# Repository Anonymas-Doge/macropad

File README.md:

# Macropad

9 key macropad with rotary encoder, OLED DISPLAY, and WS2812B LEDs. Uses QMK firmware.

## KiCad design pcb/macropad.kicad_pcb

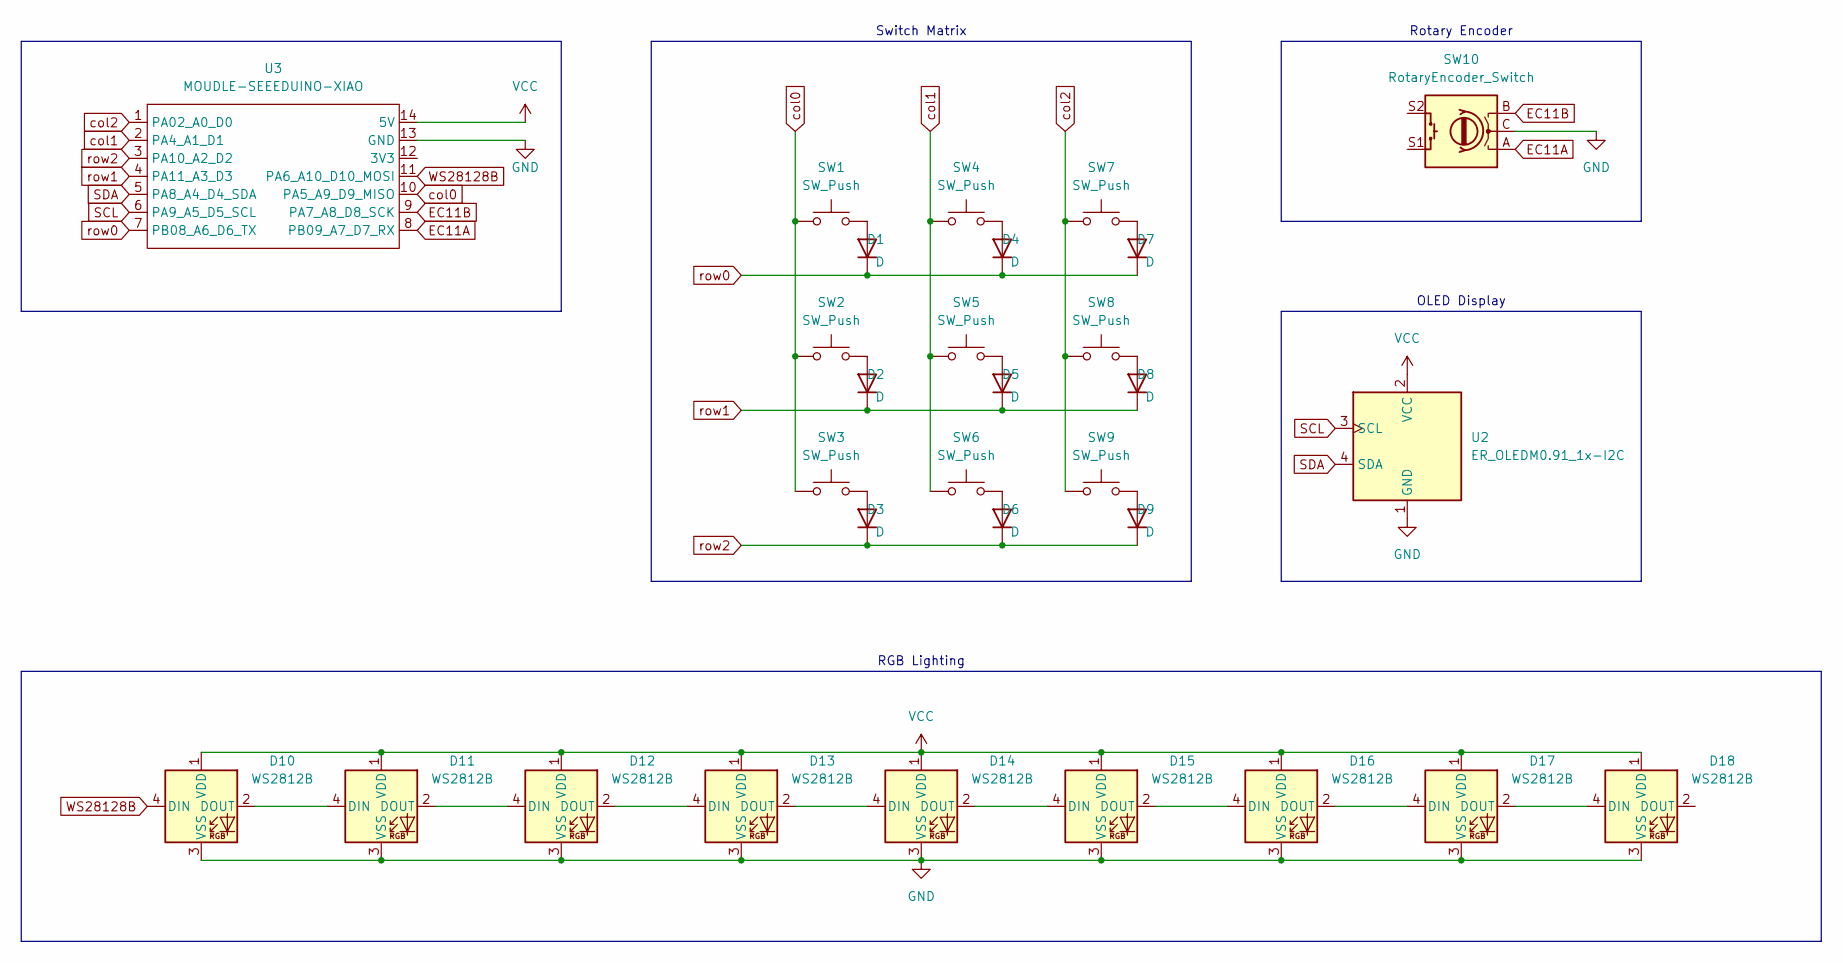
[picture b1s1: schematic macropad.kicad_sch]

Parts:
D1, D2, D3, D4, D5, D6, D7, D8, D9: D; D_DO-35_SOD27_P7.62mm_Horizontal
D10, D11, D12, D13, D14, D15, D16, D17, D18: WS2812B; SK6812MINI-E_fixed
SW1, SW2, SW3, SW4, SW5, SW6, SW7, SW8, SW9: SW_Push; SW_Cherry_MX_1.00u_PCB
SW10: RotaryEncoder_Switch; RotaryEncoder_Alps_EC11E-Switch_Vertical_H20mm
U2: ER_OLEDM0.91_1x-I2C; SSD1306-0.91-OLED-4pin-128x32
U3: MOUDLE-SEEEDUINO-XIAO; XIAO-Generic-Hybrid-14P-2.54-21X17.8MM

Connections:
EC11A: SW10.A, U3.8 (PB09_A7_D7_RX)
EC11B: SW10.B, U3.9 (PA7_A8_D8_SCK)
GND: D10.3 (VSS), D11.3 (VSS), D12.3 (VSS), D13.3 (VSS), D14.3 (VSS), D15.3 (VSS), D16.3 (VSS), D17.3 (VSS), D18.3 (VSS), SW10.C, U2.1 (GND), U3.13 (GND)
unnamed: D1.2 (A), SW1.2
unnamed: D2.2 (A), SW2.2
unnamed: D3.2 (A), SW3.2
unnamed: D4.2 (A), SW4.2
unnamed: D5.2 (A), SW5.2
unnamed: D6.2 (A), SW6.2
unnamed: D7.2 (A), SW7.2
unnamed: D8.2 (A), SW8.2
unnamed: D9.2 (A), SW9.2
unnamed: D10.2 (DOUT), D11.4 (DIN)
unnamed: D11.2 (DOUT), D12.4 (DIN)
unnamed: D12.2 (DOUT), D13.4 (DIN)
unnamed: D13.2 (DOUT), D14.4 (DIN)
unnamed: D14.2 (DOUT), D15.4 (DIN)
unnamed: D15.2 (DOUT), D16.4 (DIN)
unnamed: D16.2 (DOUT), D17.4 (DIN)
unnamed: D17.2 (DOUT), D18.4 (DIN)
SCL: U2.3 (SCL), U3.6 (PA9_A5_D5_SCL)
SDA: U2.4 (SDA), U3.5 (PA8_A4_D4_SDA)
VCC: D10.1 (VDD), D11.1 (VDD), D12.1 (VDD), D13.1 (VDD), D14.1 (VDD), D15.1 (VDD), D16.1 (VDD), D17.1 (VDD), D18.1 (VDD), U2.2 (VCC), U3.14 (5V)
WS28128B: D10.4 (DIN), U3.11 (PA6_A10_D10_MOSI)
col0: SW1.1, SW2.1, SW3.1, U3.10 (PA5_A9_D9_MISO)
col1: SW4.1, SW5.1, SW6.1, U3.2 (PA4_A1_D1)
col2: SW7.1, SW8.1, SW9.1, U3.1 (PA02_A0_D0)
row0: D1.1 (K), D4.1 (K), D7.1 (K), U3.7 (PB08_A6_D6_TX)
row1: D2.1 (K), D5.1 (K), D8.1 (K), U3.4 (PA11_A3_D3)
row2: D3.1 (K), D6.1 (K), D9.1 (K), U3.3 (PA10_A2_D2)

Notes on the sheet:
OLED Display
Switch Matrix
RGB Lighting
Rotary Encoder

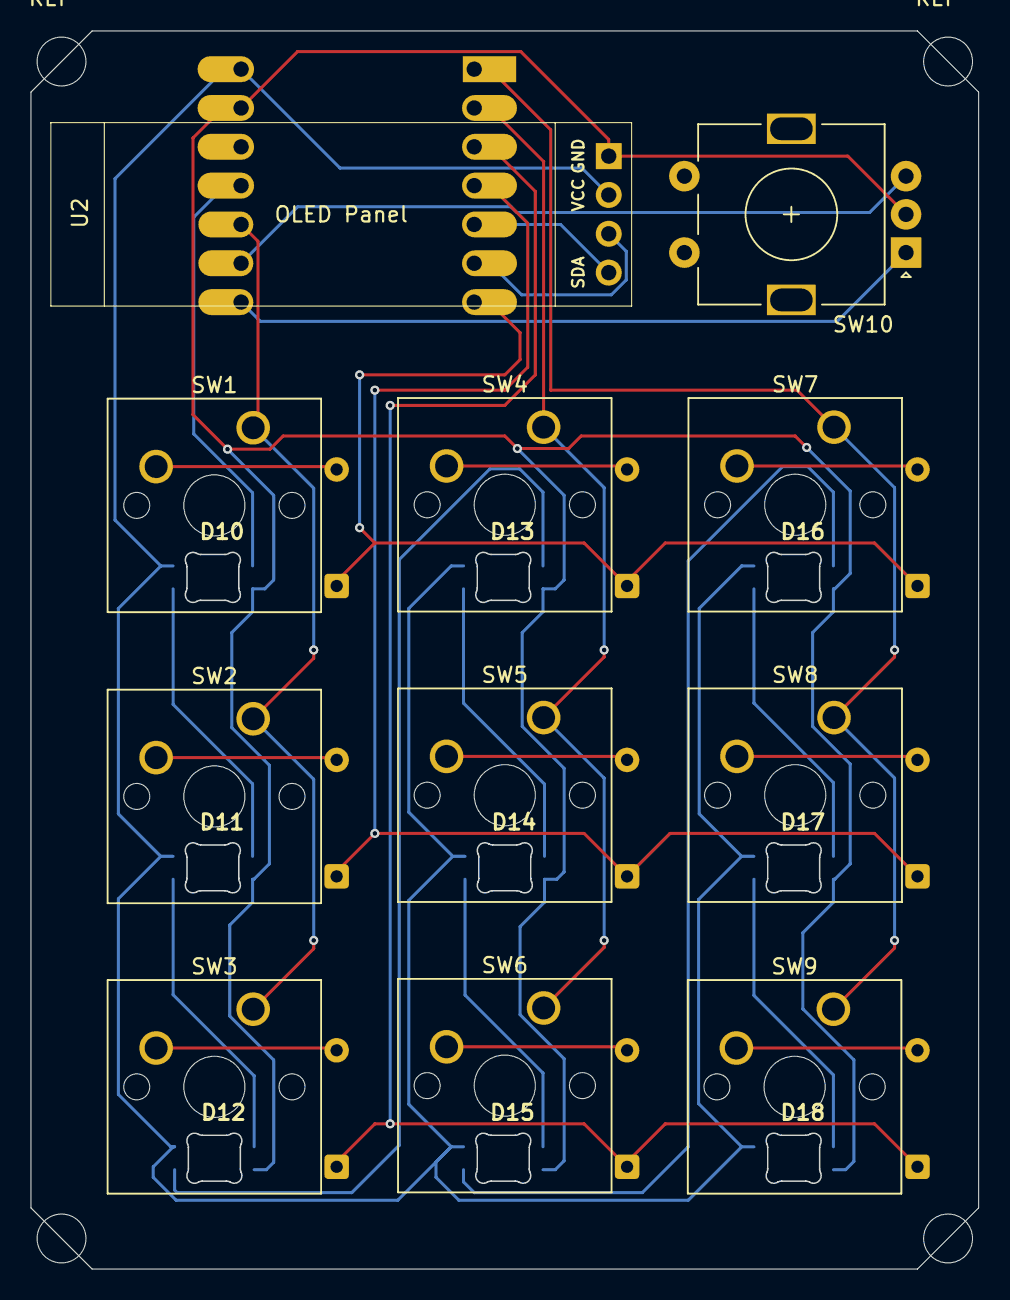
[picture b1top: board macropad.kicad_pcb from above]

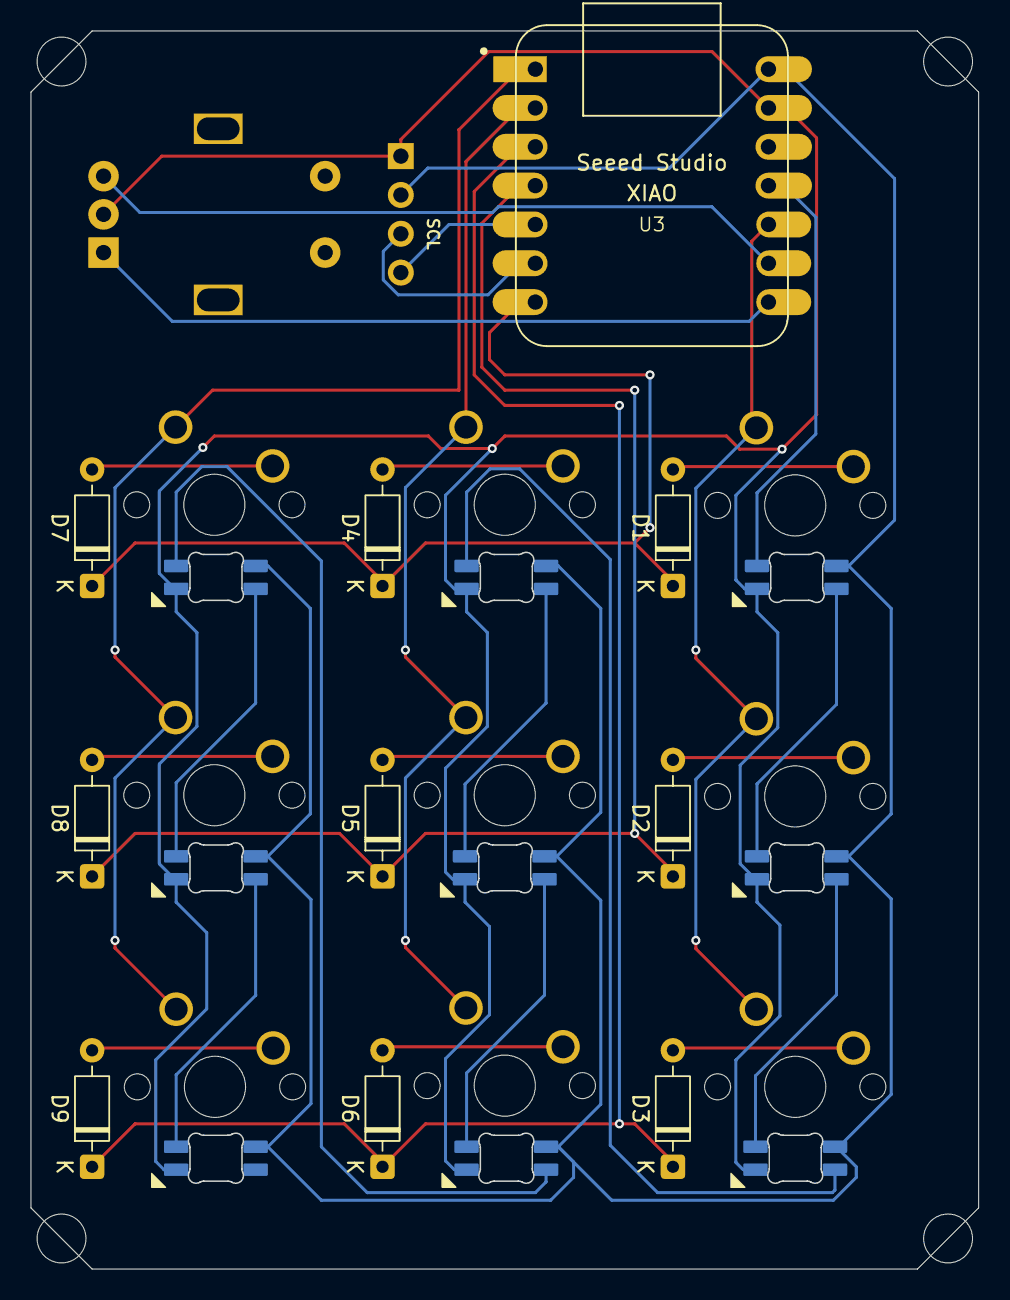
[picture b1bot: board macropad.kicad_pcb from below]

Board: 2 copper layers, 62.0 x 81.0 mm, 30 parts (10 on the bottom side), 30 nets.

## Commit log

2026-03-03 added pcb
2026-03-03 added gitignore
2026-03-03 removed .history and macropad-backups from repo
2026-03-03 added README and cad models
2026-03-05 created CAD assembly and assembled electronics and created bottom casing; also changed some electronics models
2026-03-05 updated pcb and cad to align usb port
2026-03-06 centered OLED
2026-03-06 added shell to CAD
